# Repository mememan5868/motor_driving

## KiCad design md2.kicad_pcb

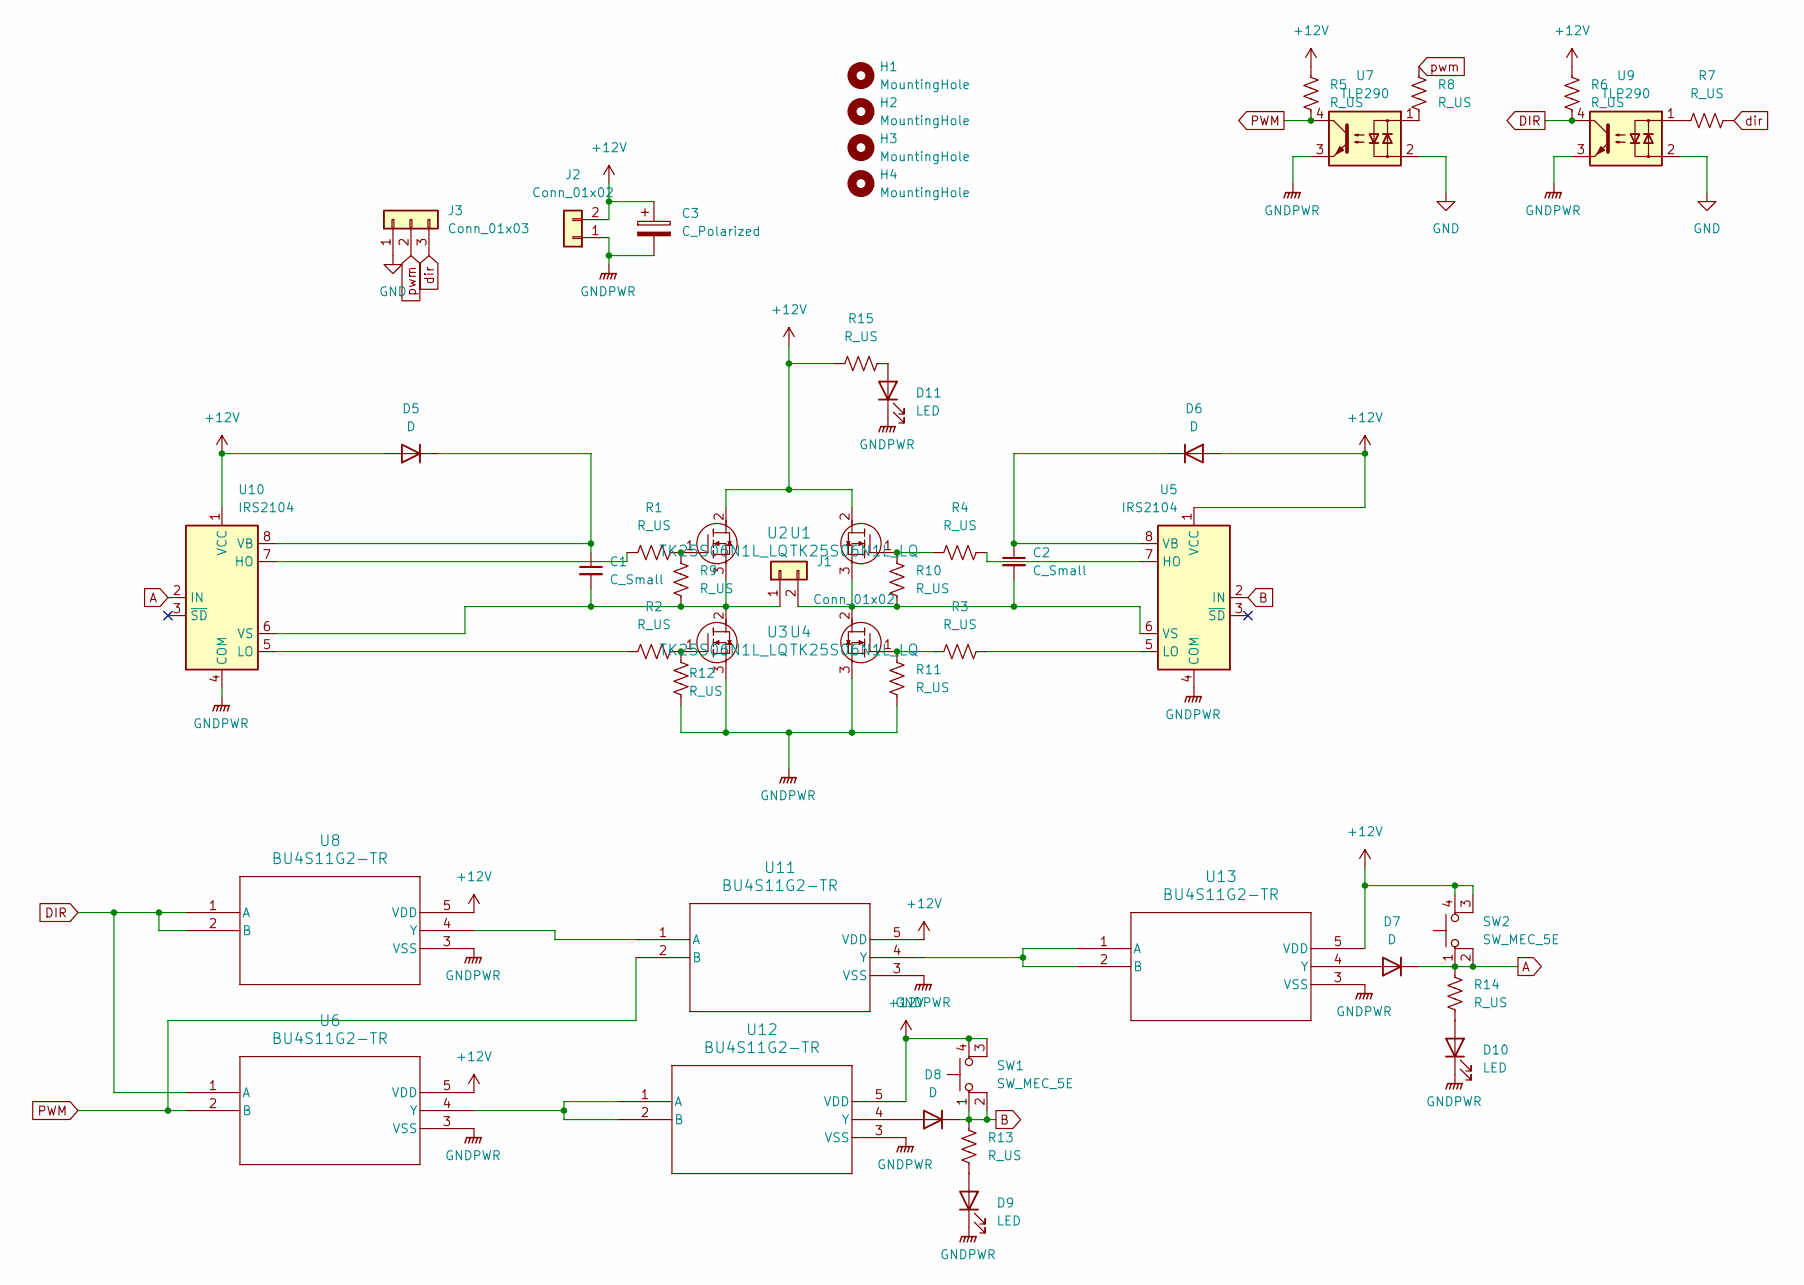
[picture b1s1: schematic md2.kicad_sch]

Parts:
C1, C2: C_Small; C_0603_1608Metric_Pad1.08x0.95mm_HandSolder
C3: C_Polarized; C_Radial_D12.5mm_H25.0mm_P5.00mm
D5, D6, D7, D8: D; D_0603_1608Metric_Pad1.05x0.95mm_HandSolder
D9, D10, D11: LED; LED_0603_1608Metric_Pad1.05x0.95mm_HandSolder
H1, H2, H3, H4: MountingHole; MountingHole_3.2mm_M3_DIN965
J1: Conn_01x02; AMASS_XT60PW-F_1x02_P7.20mm_Horizontal
J2: Conn_01x02; AMASS_XT60IPW-M_1x03_P7.20mm_Horizontal
J3: Conn_01x03; JST_XH_S3B-XH-A_1x03_P2.50mm_Horizontal
R1, R2, R3, R4, R5, R6, R7, R8, R9, R10, R11, R12, R13, R14, R15: R_US; R_0603_1608Metric_Pad0.98x0.95mm_HandSolder
SW1, SW2: SW_MEC_5E; SW_SKRPACE010
U1, U2, U3, U4: TK25S06N1L_LQ; TK25S06N1L-LQ_DPAK&plus__TOS-M
U5, U10: IRS2104; 8L-SOIC_INF
U6, U8, U11, U12, U13: BU4S11G2-TR; SSOP5_ROM
U7, U9: TLP290; SOP-4_4.4x2.6mm_P1.27mm

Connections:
+12V: C3.1, D5.2 (A), D6.2 (A), J2.2, R5.1, R6.1, R15.1, SW1.3 (K), SW1.4 (A), SW2.3 (K), SW2.4 (A), U1.2, U2.2, U5.1 (VCC), U6.5 (VDD), U8.5 (VDD), U10.1 (VCC), U11.5 (VDD), U12.5 (VDD), U13.5 (VDD)
A: D7.1 (K), R14.1, SW2.1, SW2.2, U10.2 (IN)
B: D8.1 (K), R13.1, SW1.1, SW1.2, U5.2 (IN)
DIR: R6.2, U6.1 (A), U8.1 (A), U8.2 (B), U9.4
GND: J3.1, U7.2, U9.2
GNDPWR: C3.2, D9.1 (K), D10.1 (K), D11.1 (K), J2.1, R11.1, R12.1, U3.3, U4.3, U5.4 (COM), U6.3 (VSS), U7.3, U8.3 (VSS), U9.3, U10.4 (COM), U11.3 (VSS), U12.3 (VSS), U13.3 (VSS)
unnamed: C1.1, D5.1 (K), U10.8 (VB)
unnamed: C2.1, D6.1 (K), U5.8 (VB)
unnamed: D7.2 (A), U13.4 (Y)
unnamed: D8.2 (A), U12.4 (Y)
unnamed: D9.2 (A), R13.2
unnamed: D10.2 (A), R14.2
unnamed: D11.2 (A), R15.2
unnamed: C1.2, J1.1, R9.1, U1.3, U4.2, U10.6 (VS)
unnamed: C2.2, J1.2, R10.1, U2.3, U3.2, U5.6 (VS)
unnamed: R1.2, R9.2, U1.1
unnamed: R7.1, U9.1
unnamed: R8.1, U7.1
unnamed: R4.1, R10.2, U2.1
unnamed: R3.1, R11.2, U3.1
unnamed: R2.2, R12.2, U4.1
unnamed: R4.2, U5.7 (HO)
unnamed: R3.2, U5.5 (LO)
unnamed: R1.1, U10.7 (HO)
unnamed: R2.1, U10.5 (LO)
unnamed: U8.4 (Y), U11.1 (A)
unnamed: U11.4 (Y), U13.1 (A), U13.2 (B)
unnamed: U6.4 (Y), U12.1 (A), U12.2 (B)
PWM: R5.2, U6.2 (B), U7.4, U11.2 (B)
dir: J3.3, R7.2
pwm: J3.2, R8.2

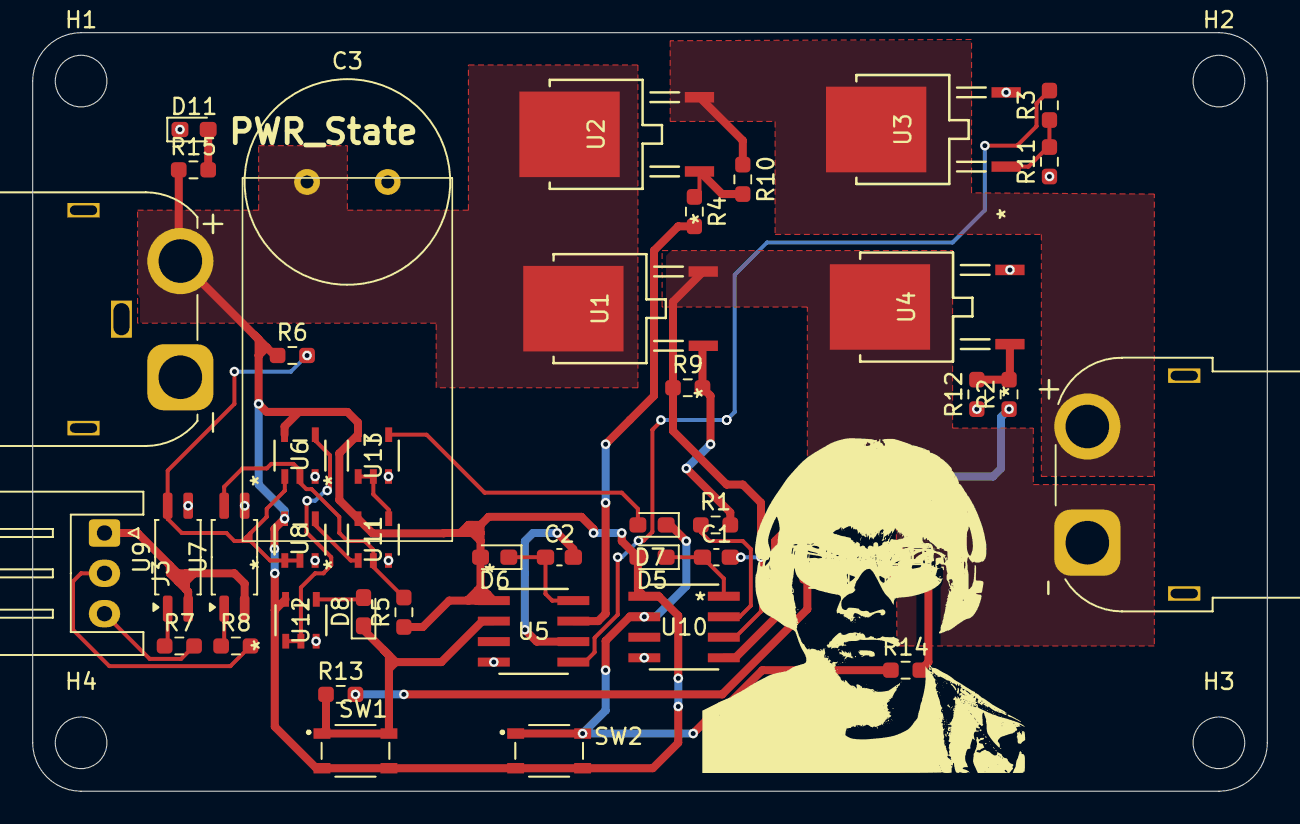
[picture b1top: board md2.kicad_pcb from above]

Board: 2 copper layers, 76.5 x 47.0 mm, 47 parts (0 on the bottom side), 31 nets.
